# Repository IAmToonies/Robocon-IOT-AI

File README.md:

# Robocon-IOT-AI
### Require
- [Eagle Cad](https://www.autodesk.com/products/eagle/overview?term=1-YEAR&tab=subscription)
- C/C++
- [Replit - to code online](https://replit.com/~)

### Learn
- [H-Bridge Circuit](https://www.youtube.com/watch?v=JkspuxiViNM&list=PLY4yL8CZKCYxgLQgCdkcOXX4D8s_VrgWl&index=3&ab_channel=EngineersDream)
- Pulse Width Modulation

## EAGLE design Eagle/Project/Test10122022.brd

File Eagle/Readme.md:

- Down and add Libraries into Eagle

# Setup Frame:
- Step 1: Create new schematic --> Rename file: Test10122022.sch  [Testday.sch]
- Step 2: Click `Add Part` (On the left) --> Search: frame --> A3L-LOC
- Step 3: Grid (Left above) --> Size: 2.54/1.57 mm & Alt: 1 mm --> Line --> On 

# Add Part (Thêm linh kiện):
- Step 1: `Add Part` --> Search: R0603
- Step 2: Change value: Click `Value` (Below `Add Part`) --> click center R0603 --> Change: 2K2 (Value)
- Step 3: Choose Led0603 --> Value: P_5V
- Step 4: Connect two part: 'Net' (Left Above `Value`)
- Step 5: Click `Generate/switch to board` (Above near `print`)

# Generate/switch to board
- Step 1: Grid --> Size: 10(board) mm & Alt: 0.127 mm --> On
- Step 2: Change Size Board: 5x5 block
- Step 3: Lỗ bắt ốc: `via` --> lỗ 3ly: Drill 3 & viền 5: Diameter 5
- Drill --> Size: 0.15875 để đi layout linh kiện dán / 2.54 ~ Rào cái
- Xoay linh kiện --> Chuột phải. Chuyển lớp linh kiện dán phía sau --> click con lăn
- Yellow line --> We need to place them so that the yellow lines **dont overlap**
- Vẽ dây: Route Airwire --> Width [0.25 - 1] mm // Dây công suất => **1** mm // Dây tín hiệu => **0.25** mm // Để kết kết nối 2 mặt  --> click con lăn --> Chọn vòng tròn
- Text --> To put Name --> Font: Vector // Ratio: 15

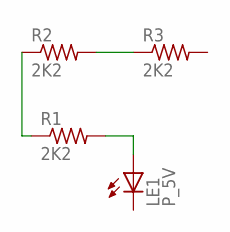
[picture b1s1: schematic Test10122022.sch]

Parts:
LE1: P_5V; 0603P
R1, R2, R3: 2K2; R0603

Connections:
unnamed: LE1.2 (A), R1.2
unnamed: R1.1, R2.1
unnamed: R2.2, R3.1

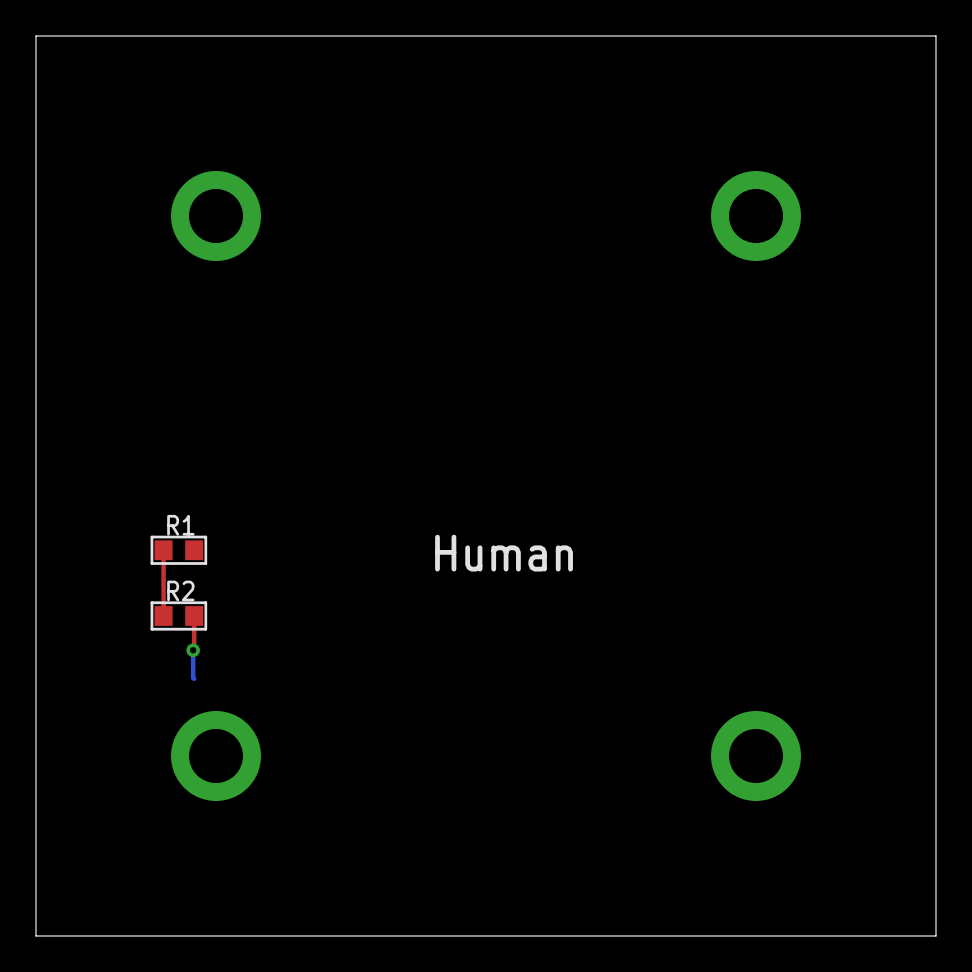
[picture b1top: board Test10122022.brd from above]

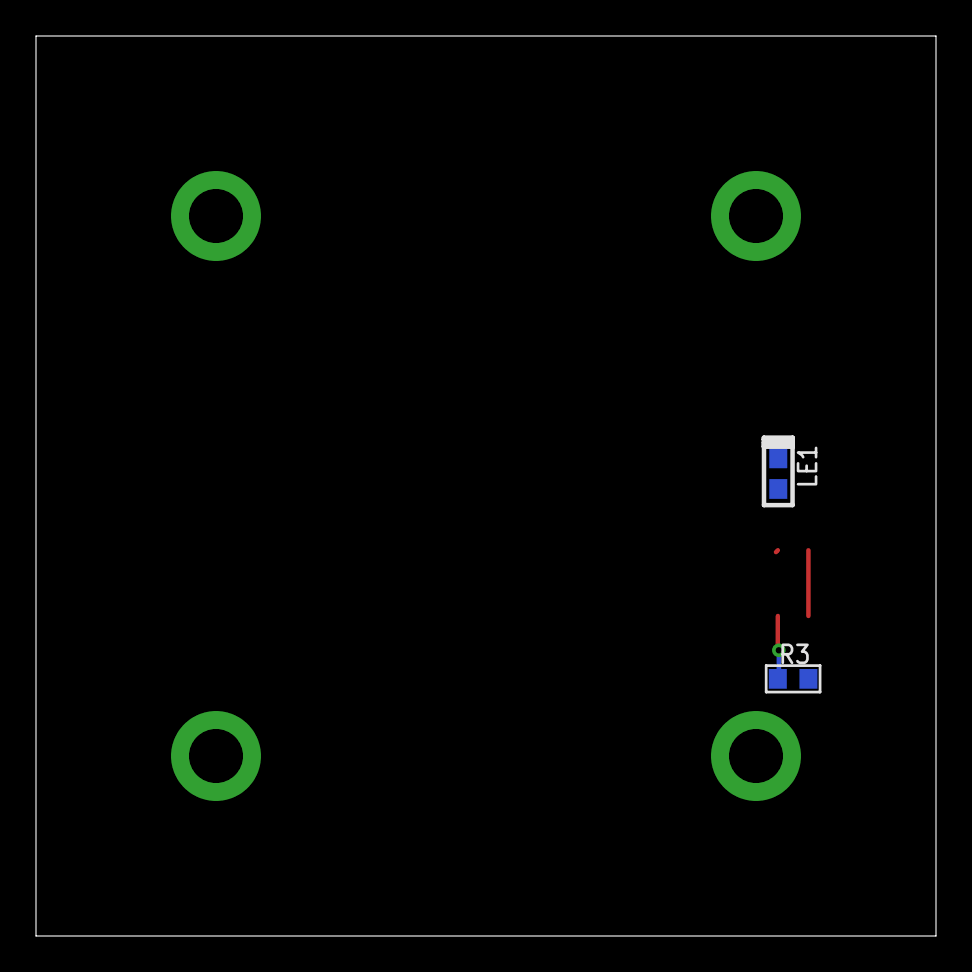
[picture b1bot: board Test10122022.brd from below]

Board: 2 copper layers, 50.0 x 50.0 mm, 4 parts (2 on the bottom side), 3 nets.

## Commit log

2022-12-11 Add files via upload
    Libraries For down Eagle
2022-12-11 Rename UseEagle.md to Readme.md
2023-01-01 Create Learn-Micro
2023-01-01 Create asd
